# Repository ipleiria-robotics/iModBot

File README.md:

# Apresentação do Projeto 
Este projeto iModBot consiste num robô modular de baixo custo que pode ser programado através de liguagem de programação por blocos e/ou através de linguagem C/C++. Este projeto dispõe de uma biblioteca para facilitar o controlo do robô. 

A programação por blocos divide-se em 4 níveis, para facilitar a aprendizagem do utilizadores. Os níveis são os seguintes:
 - Nível Iniciante -> É possível colocar o robô a efetuar uma terefa com 1 a 2 blocos.
 - Nível Normal -> O utilizador tem mais controlo sob o movimento do robô, dispõe apenas da função loop.
 - Nível Médio -> O utilizador pode agora colocar blocos na função Setup e Loop.
 - Nível Avançado -> O utilizador dispõe de todas as funções da biblioteca e necessita de configurar todos os aspetos do robô.

# Como transferir ficheiros do GitHub
No GitHub não é possível transferir qualquer ficheiro individualmente. É recomendado transferir todas as pastas e ficheiros presentes neste projeto. Para tal siga as instruções abaixo:

Comece por transferir todos os ficheiros no formato .zip

Abra a localização do ficheiro .zip transferido e use um programa para extrair os conteudos

Por fim irá obter um conjunto de pastas e ficheiros organizados da mesma maneira que se encontram neste repositório.

# Elaboração do Projeto
**1º Passo do Projeto**

Para montar o robô basta seguir o documento 4_Guia_de_montagem_offline ([3_Documentacao/3-4_Guia_de_montagem_offline.pdf](https://github.com/ipleiria-robotics/iModBot/blob/master/3_Documentacao/3-4_Guia_de_montagem_offline.pdf)) que mostra como montar ou então assistir o video [iModBot@ipleiria.pt guia de montagem](https://www.youtube.com/watch?v=i4wFh0GqzkM&feature=emb_logo). Este documento também inclui uma listagem de componentes
que serão necessários para a sua montagem. Para perceber melhor o que faz cada componente do robô pode ler o manual técnico ([3_Documentacao/3-5_Manual_Tecnico_iModBot.pdf](https://github.com/ipleiria-robotics/iModBot/blob/master/3_Documentacao/3-5_Manual_Tecnico_iModBot.pdf)) que explica vários aspetos do robô. 

Lista de material:
 * ESP32 wroom32 devkit ; 

 * l293d 4 channel module ;

 * 2x LM393 speed sensor ; 

 * BFD-1000 5CH ;

 * HC-SR04 ;

 * I2C level shifter ; 

 * TP4056 ; 

 * MT3608 ; 

 * li-ion rechargable battery 2500 mAh ; 

 * 2x Breadboard 400 ; 

 * Jumper wire male male, Jumper wire male female ; 

 * 2wd smart robot kit . 

**2º Passo do Projeto** 
 
 Downloads:
 
- Biblioteca iModBot.zip ([4_Biblioteca/iModBot.zip](https://github.com/ipleiria-robotics/iModBot/blob/master/4_Biblioteca/iModBot.zip)) e descompacta o ficheiro. 

- Software Arduino IDE na [pagina do Arduino](https://www.arduino.cc/en/main/software), instale a versão que se adequa ao seu equipamento, para windows recomendamos a opção "Windows installer, for windows 7 and up". 
 -- Tenha em atenção que os conteudos do projeto foram desenvolvidos e testados na versão Arduino IDE 1.8.12, os mesmos deverão continuar ser compatíveis com as versões mais recentes deste software.

- Ficheiro java do ArduBlock ([5_AduBlock/ardublock-beta-20200614.jar](https://github.com/ipleiria-robotics/iModBot/blob/master/5_AduBlock/ardublock-beta-20200614.jar)).

**3º Passo do Projeto**

Ler e seguir os tutoriais para configurar o Arduíno:
 - Configurar Arduíno IDE para o ESP32; ([3_Documentacao/3-1_Como_comunicar_com_o_ESP32.pdf](https://github.com/ipleiria-robotics/iModBot/blob/master/3_Documentacao/3-1_Como_comunicar_com_o_ESP32.pdf))

 - Configurar ArduBlock no Arduíno IDE; ([3_Documentacao/3-2_Como_instalar_ArduBlock_no_Arduino_IDE.pdf](https://github.com/ipleiria-robotics/iModBot/blob/master/3_Documentacao/3-2_Como_instalar_ArduBlock_no_Arduino_IDE.pdf))

 - Como instalar bibliotecas no Arduíno IDE. ([3_Documentacao/3-3_Como_instalar_bibliotecas_no_Arduino_IDE.pdf](https://github.com/ipleiria-robotics/iModBot/blob/master/3_Documentacao/3-3_Como_instalar_bibliotecas_no_Arduino_IDE.pdf))

# Documentação

Após ter o Arduino IDE e o ArduBlock instalados pode usufruir dos tutoriais disponibilizados. Estes tutoriais ensinam a trabalhar com o robô sendo os mesmos divididos em duas categorias: tutoriais para ArduBlock e tutoriais para Arduino IDE.

**Documentação do ArduBlock**

Os [4 níveis](https://github.com/ipleiria-robotics/iModBot/tree/master/1_Tutoriais/1-1_Tuturiais_para_ArduBlock) a baixo irão facilitar e guiar como deve de utilizar cada bloco e como criar um programa.

- [Nivel Iniciante;](https://github.com/ipleiria-robotics/iModBot/blob/master/1_Tutoriais/1-1_Tuturiais_para_ArduBlock/Tutorial_1_-_Nivel%20iniciante/Nivel_iniciante.pdf)

- [Nivel Normal;](https://github.com/ipleiria-robotics/iModBot/blob/master/1_Tutoriais/1-1_Tuturiais_para_ArduBlock/Tutorial_2_-_Nivel_Normal/Nivel_Normal.pdf)

- [Nivel Médio;](https://github.com/ipleiria-robotics/iModBot/blob/master/1_Tutoriais/1-1_Tuturiais_para_ArduBlock/Tutorial_3_-_Nivel_Medio/Nivel_Medio.pdf)

- [Nivel Avançado;](https://github.com/ipleiria-robotics/iModBot/blob/master/1_Tutoriais/1-1_Tuturiais_para_ArduBlock/Tutorial_4_-_Nivel_Avancado/Nivel_Avancado.pdf)

Existe um conjunto de atividades para cada nível. Após ler a documentação de um nível poderá realizar a atividade correspondente  ao mesmo em [2_Atividades/2-1_Atividades_para_ArduBlock/](https://github.com/ipleiria-robotics/iModBot/tree/master/2_Atividades/2-1_Atividades_para_ArduBlock).

**Documentação do Arduino IDE**

Depois de já ter realizado os tutoriais do ArduBock deverá ter uma noção melhor de como programar no Arduino IDE. Também elaboramos alguns tutoriais e atividades para facilitar a aprendizagem,

- [Tutorial 1 - Movimento;](https://github.com/ipleiria-robotics/iModBot/blob/master/1_Tutoriais/1-2_Tutoriais_para_Arduino_IDE/Tutorial_1_-_Movimento/Tutorial_1_iModBot_-_Movimento.pdf)

- [Tutorial 2 - Sensores;](https://github.com/ipleiria-robotics/iModBot/blob/master/1_Tutoriais/1-2_Tutoriais_para_Arduino_IDE/Tutorial_2_-_Sensores/Tutorial_2_iModBot_-_Sensores.pdf)

- [Tutorial 3 - Seguir trajeto.](https://github.com/ipleiria-robotics/iModBot/blob/master/1_Tutoriais/1-2_Tutoriais_para_Arduino_IDE/Tutorial_3_-_Seguir_trajeto/Tutorial_3_iModBot_-_Seguir%20trajeto.pdf)

As atividades para cada tutorial estão disponíveis em [/2_Atividades/2-2_Atividades_para_Arduino_IDE/
](https://github.com/ipleiria-robotics/iModBot/tree/master/2_Atividades/2-2_Atividades_para_Arduino_IDE).

# Editar o ArduBlock

Caso tenha interesse em criar um bloco deve seguir os passos neste pasta [5.Ardublock](https://github.com/ipleiria-robotics/iModBot/blob/master/5_AduBlock/README.md)

# Realidade Aumentada

Utilizando o motor de jogos Unity3d, ROS2 e a nossa biblioteca para o robô, cria o teu mundo virtual, projeta-o no mundo real e vê o robô a interagir com ele.
Esta funcionalidade ainda está em desenvolvimento sendo que por agora ainda é muito limitada. 

# Controladores remotos

Com os controladores das consolas populares PS3 e PS4, consegue controlar o robot à distância via bluetooth. A biblioteca é fácil de instalar e apenas necessita de um programa, o Arduino IDE. Basta colocar valores desejados no código, tanto como sensibilidade de direção, aceleração dos motores, velocidade máxima, e muito mais!

# Autores
 
- Abel Teixeira   - estudante do [Politécnico de Leiria](https://www.ipleiria.pt/cursos/) do curso TeSP em Eletrónica e Redes de Telecomunicações, GitHub: [Ab-Tx](https://github.com/Ab-Tx)
- Samuel Lourenço - estudante do [Politécnico de Leiria](https://www.ipleiria.pt/cursos/) do curso TeSP em Automação, Robótica e manutenção Industrial, GitHub: [SamueLourenc0](https://github.com/SamueLourenc0)
- Nelson Henriques - estudante do [Politécnico de Leiria](https://www.ipleiria.pt/cursos/) do curso TeSP em Automação, Robótica e manutenção Industrial, GitHub: [NetchoExtreme](https://github.com/NetchoExtreme)
- Paulo Sousa - estudante do [Politécnico de Leiria](https://www.ipleiria.pt/cursos/) do curso TeSP em Eletrónica e Redes de Telecomunicações, GitHub [DimitriOnLSD](https://github.com/DimitriOnLSD)

## Orientado por:
- Luís Conde - [Politécnico de Leiria](https://www.ipleiria.pt), GitHub: [Luís Conde](https://github.com/conde-ISR-UC-PT)
- Carlos Neves - [Politécnico de Leiria](https://www.ipleiria.pt), [INESC-Coimbra](http://inescc.estg.ipleiria.pt/), GitHub: [Carlos Neves](https://github.com/carlos-neves)

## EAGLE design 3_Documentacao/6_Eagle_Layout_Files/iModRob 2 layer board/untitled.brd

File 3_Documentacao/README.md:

# Documentação

Nesta pasta pode encontrar documentação para varios aspetos do projeto.

- **3.1_Como_comunicar_com_o_ESP32.pdf**
  - Explica como conectar a placa de desenvolvimento ESP32 ao software Arduino IDE.
  
- **3.2_Como_instalar_ArduBlock_no_Arduino_IDE.pdf**
  - Explica como instalar o ArduBlock no software Arduino IDE.
  
- **3.3_Como_instalar_bibliotecas_no_Arduino_IDE.pdf**
  - Explica como instalar biblioteacas no software Arduino IDE.
  
- **3.4_Guia_de_montagem_offline.pdf**
  - Fornece uma lista de componentes e apresenta as ligações que devem ser efetuadas entre os componentes.
  
- **3.5_Manual_Tecnico_iModBot.pdf**
  - Descreve os componentes utilizados no projeto, as funções proporcionadas pela biblioteca entre outros aspetos.
  
- **3.6_iModRob_Eagle_2_layer_board.zip**
  - Também é disponibilizado o projeto para a aplicação Autodesk Eagle que contém uma placa de circuito impresso (PCB) que facilitará a montagem dos componentes no robô.

- **3.7_Listagem_de_componentes_mais_links_de_compra_auxiliares**
  - Também é disponibilizado uma lista de componentes completa a incluir links de lojas online onde poderas encontrar os componentes em custos mais baratos.

- **3.8_ArduBlock2020**
  - Para começar a programar o robô por blocos, basta seguir o tutorial 3.3_Como_instalar_ArduBlock_no_Arduino_IDE.pdf e deve ser usado este ficheiro para ter os blocos prontos para programar o robô.

- **3.8_Guia_basica_de_montagem_de_circuitos_eletricos**
  - É fornecida uma guia basica de montagem para conhecer a Breadboard e o seu funcionamento de face à montagem de placas eletrónicas nesta ferramenta.
  
# Esquema eletrónico e PCB

  - Foram inseridos vários pontos de teste na placa de circuito impresso. 
  - Foram adicionados jumpers para poder desconectar a alimentação geral do circuito e/ou a alimentação da placa de desenvolvimento DOIT ESP32 Devkit V1 e/ou a alimentação do módulo baseado no integrado L293D.

**Esquema eletrónico**:

**Placa de circuito impresso** (sem o plano de massa visível):

    Uma boa opção para conectar/desconectar a alimentação seria o uso de conectores "jumper two pins".

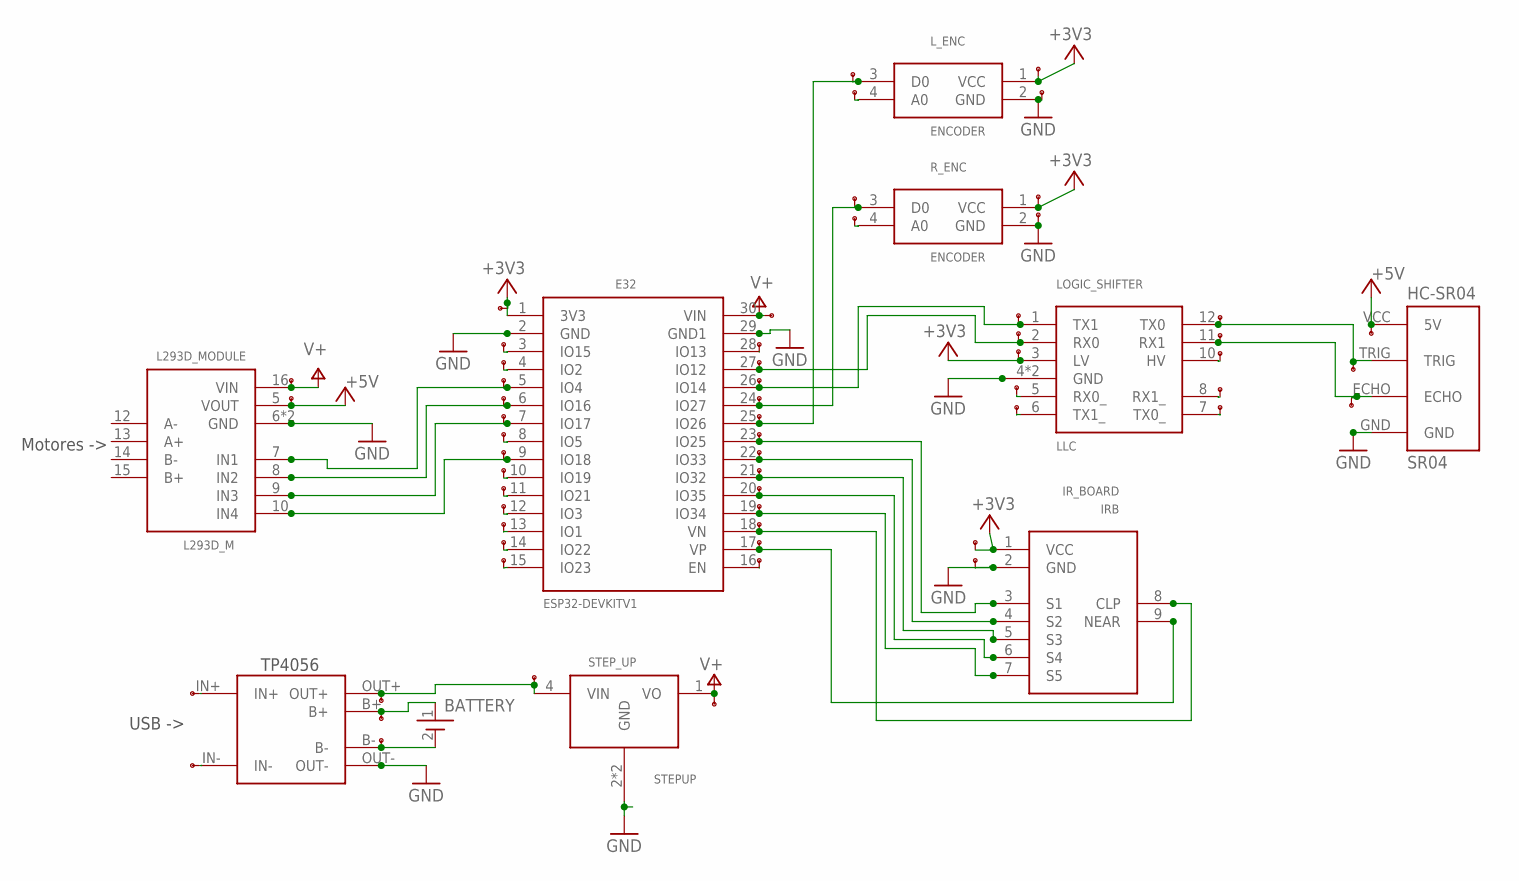
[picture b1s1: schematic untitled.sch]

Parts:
BATTERY: BAT_PAD
BAT_CHARGER: TP4056-MODULE; TP4056-LITHIUM-PROTECTED-MODULE
E32: ESP32DEVKITV1; ESP32-DEVKITV1
IR_BOARD: IRB
L293D_MODULE: L293D_M
LOGIC_SHIFTER: LLC
L_ENC: ENCODER
R_ENC: ENCODER
SR04: HC-SR04; HC-SR04_FOOTPRINT
STEP_UP: STEPUP
U$1, U$2, U$3, U$4, U$8, U$10, U$11, U$12, U$13, U$14, U$15, U$16, U$17, U$18, U$19, U$20, U$21, U$22, U$23, U$24, U$25, U$26, U$27, U$28, U$29, U$30, U$31, U$32, U$33, U$34, U$36, U$37, U$38, U$40, U$41, U$42, U$43, U$44, U$46, U$47, U$48, U$49, U$50, U$51, U$52, U$53, U$54, U$55, U$56, U$57, U$59, U$60, U$61, U$62, U$63, U$64, U$65, U$67, U$68, U$69: TP

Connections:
+3V3: E32.1 (3V3), IR_BOARD.1 (VCC), LOGIC_SHIFTER.3 (LV), L_ENC.1 (VCC), R_ENC.1 (VCC), U$3.P$1, U$8.P$1, U$49.P$1, U$51.P$1, U$57.P$1
+5V: L293D_MODULE.5 (VOUT), SR04.VCC (5V), U$2.P$1, U$69.P$1
GND: BAT_CHARGER.OUT-, E32.2 (GND), E32.29 (GND1), IR_BOARD.2 (GND), L293D_MODULE.6 (GND), L293D_MODULE.11 (GND), LOGIC_SHIFTER.4 (GND), LOGIC_SHIFTER.9 (GND), L_ENC.2 (GND), R_ENC.2 (GND), SR04.GND, STEP_UP.2 (GND), STEP_UP.3 (GND), U$4.P$1, U$50.P$1, U$52.P$1
unnamed: E32.5 (IO4), L293D_MODULE.7 (IN1), U$46.P$1
unnamed: E32.6 (IO16), L293D_MODULE.8 (IN2), U$12.P$1
unnamed: E32.7 (IO17), L293D_MODULE.9 (IN3), U$13.P$1
unnamed: E32.9 (IO18), L293D_MODULE.10 (IN4), U$15.P$1
unnamed: BATTERY.1 (+), BAT_CHARGER.B+, U$41.P$1
unnamed: BATTERY.2 (-), BAT_CHARGER.B-, U$40.P$1
unnamed: BAT_CHARGER.OUT+, STEP_UP.4 (VIN), U$42.P$1, U$43.P$1
unnamed: E32.23 (IO25), IR_BOARD.3 (S1), U$29.P$1
unnamed: E32.22 (IO33), IR_BOARD.4 (S2), U$28.P$1
unnamed: E32.21 (IO32), IR_BOARD.5 (S3), U$27.P$1
unnamed: E32.20 (IO35), IR_BOARD.6 (S4), U$26.P$1
unnamed: E32.19 (IO34), IR_BOARD.7 (S5), U$25.P$1
unnamed: E32.17 (VP), IR_BOARD.9 (NEAR), U$23.P$1
unnamed: E32.18 (VN), IR_BOARD.8 (CLP), U$24.P$1
unnamed: E32.27 (IO12), LOGIC_SHIFTER.2 (RX0), U$33.P$1, U$56.P$1
unnamed: E32.26 (IO14), LOGIC_SHIFTER.1 (TX1), U$32.P$1, U$55.P$1
unnamed: LOGIC_SHIFTER.12 (TX0), SR04.TRIG, U$65.P$1, U$68.P$1
unnamed: LOGIC_SHIFTER.11 (RX1), SR04.ECHO, U$64.P$1, U$67.P$1
unnamed: E32.24 (IO27), R_ENC.3 (D0), U$31.P$1, U$54.P$1
unnamed: E32.25 (IO26), L_ENC.3 (D0), U$30.P$1, U$47.P$1
unnamed: E32.15 (IO23), U$21.P$1
unnamed: E32.3 (IO15), U$10.P$1
unnamed: E32.4 (IO2), U$11.P$1
unnamed: E32.8 (IO5), U$14.P$1
unnamed: E32.10 (IO19), U$16.P$1
unnamed: E32.11 (IO21), U$17.P$1
unnamed: E32.12 (IO3), U$18.P$1
unnamed: E32.13 (IO1), U$19.P$1
unnamed: E32.14 (IO22), U$20.P$1
unnamed: E32.16 (EN), U$22.P$1
unnamed: E32.28 (IO13), U$34.P$1
unnamed: BAT_CHARGER.IN-, U$38.P$1
unnamed: BAT_CHARGER.IN+, U$37.P$1
unnamed: LOGIC_SHIFTER.5 (RX0_), U$59.P$1
unnamed: LOGIC_SHIFTER.6 (TX1_), U$60.P$1
unnamed: LOGIC_SHIFTER.7 (TX0_), U$61.P$1
unnamed: LOGIC_SHIFTER.8 (RX1_), U$62.P$1
unnamed: LOGIC_SHIFTER.10 (HV), U$63.P$1
unnamed: R_ENC.4 (A0), U$53.P$1
unnamed: L_ENC.4 (A0), U$48.P$1
V+: E32.30 (VIN), L293D_MODULE.16 (VIN), STEP_UP.1 (VO), U$1.P$1, U$36.P$1, U$44.P$1

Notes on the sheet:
USB ->
Motores ->
TP4056

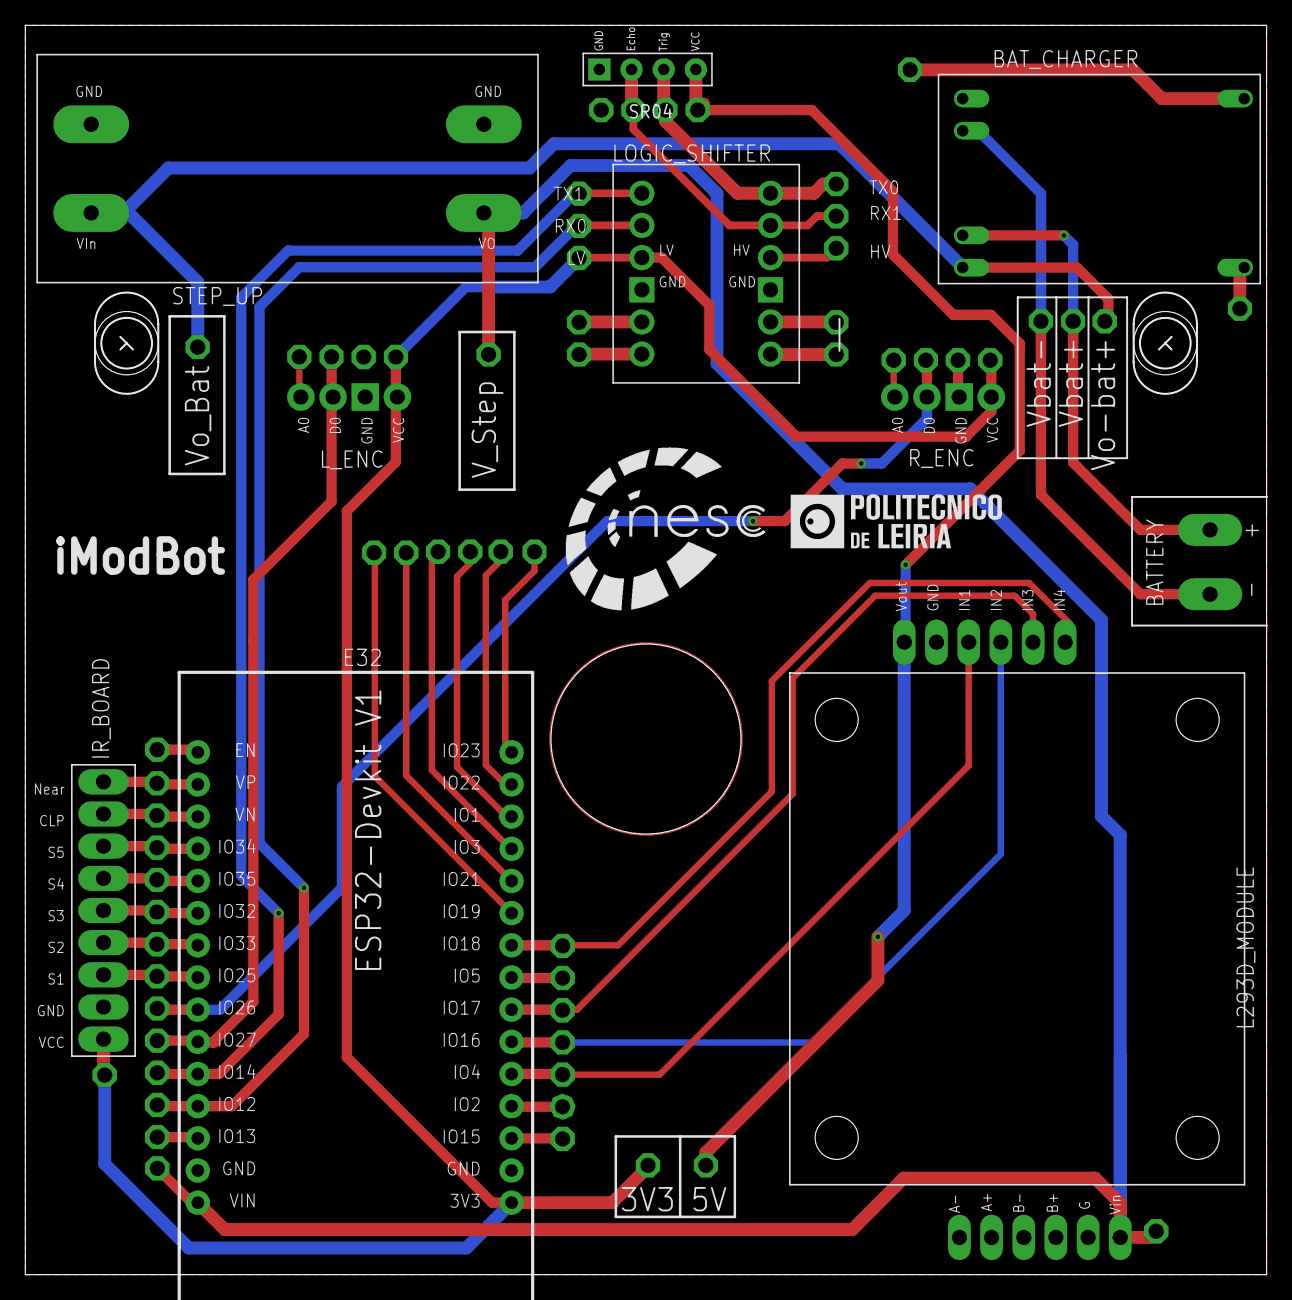
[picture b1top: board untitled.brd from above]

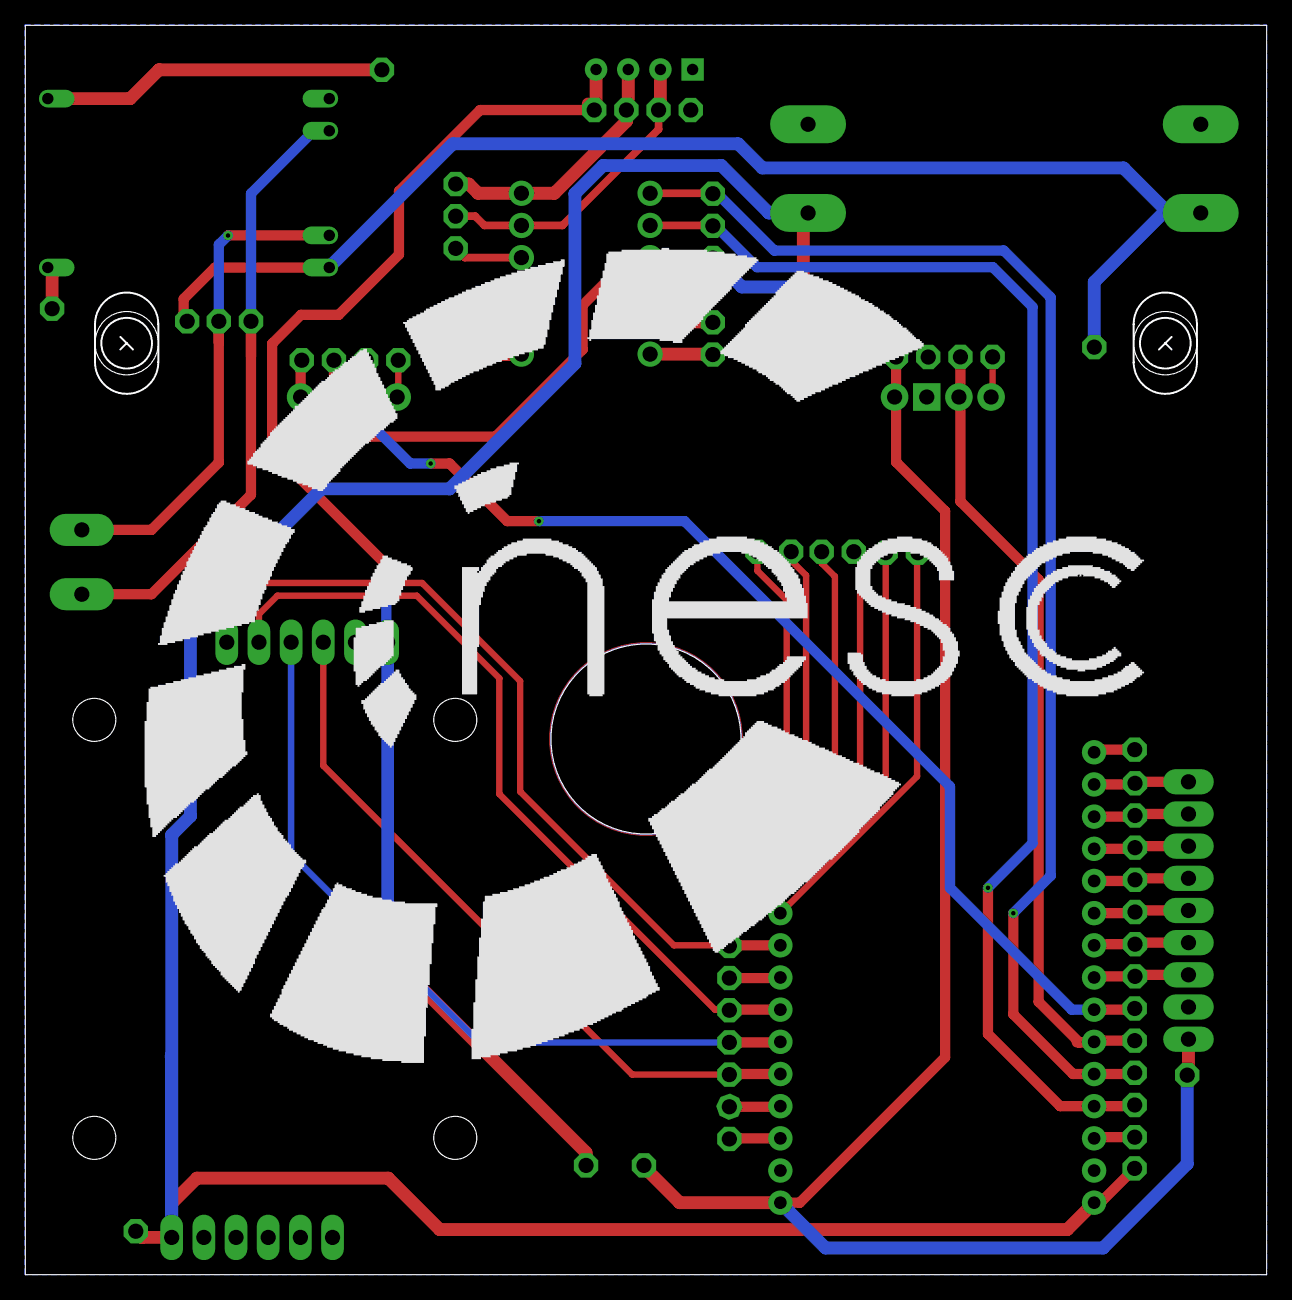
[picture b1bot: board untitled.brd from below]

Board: 2 copper layers, 97.8 x 98.5 mm, 70 parts (2 on the bottom side), 44 nets.

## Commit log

2020-06-08 structure upload
2020-06-08 Docs update
2020-06-08 new files upload
2020-06-09 Multiple files upload
2020-06-12 content match
2020-06-12 lib update
2020-06-12 mensagem
2020-06-25 Eagle project update
2020-06-25 Tutorial 1 update
2020-06-25 Names of tutorial files changed
2020-06-25 Tutorial 2 update
2020-06-25 Tutorial 3 update
2020-06-25 ArduBlock Tutorial name changes
2020-06-25 ArduBlock Activities name changes
2020-06-25 Tut 1 files update
2020-06-25 Activity 2 update
2020-06-25 Activities update
2020-06-26 file updated
2020-06-26 decription files added
2020-06-26 name changes
2020-06-26 description added
2020-06-29 library examples update
2020-06-29 examples updated
2020-07-02 Tutorials update
2020-07-09 Eagle Files updated
2020-12-09 Create Robo
2020-12-19 Bugfix
2021-03-12 Add files
2021-03-12 Upload tutorials
2021-07-15 reverse bugfix
2021-07-15 Update Tuturiais
2021-07-15 Update atividades
2021-07-15 Update documentacao
2021-07-15 update ardublock
2021-07-15 add realidade aumentada
2021-07-15 Tutorial update
2021-07-25 Add Links
2021-08-02 missing lib and fmod fix
2022-06-21 spelling
    spelling correction
2022-06-21 Updated tutorials
    Switched original language to English
2022-06-21 Updated activities
    Switched original language to English
2022-06-21 Updated documents
    Documents folder now contains all pdf's necessary to implement a functional iModBot or help the user in troubleshooting
2022-06-21 Added files
    Added folder files to easier use
    PCB files
    Battery Case 3D files
    Libraries
    Ardublock files
2022-06-21 Updated AR folder
    AR folder only
2022-06-21 Updated documents
    spelling error
2022-06-23 bug fix ramp generator
    Fixed a bug with ramp generator not accepting values
    Added non .rar files
2022-06-23 double battery case v2
    Improved version for Double battery case
2022-06-24 removed old versions
2022-06-24 update bc
2022-06-24 update battery case
2022-06-24 dualshock guide
2022-06-24 version 2 EAGLE sch
2022-06-24 update readme
    Updated PCB Files readme.md
    Updated Libraries readme.md
    Updated ArduBlock readme.md
2022-06-24 update readme
    Added new author
    Added new title for the controllers and some information
2022-06-24 update docs
    Better organization inside Documents folder
2022-06-28 update tutorials
    Added source docx files
2022-06-28 update activities
    Added source docx files
2022-06-28 update documents
    Added various documents
    Added source docx files
2022-06-28 update files
    Added PCB Files
    Added battery case files
    Added ArduBlock files
    Added libraries
    Update readme file
2022-06-28 update AR
    Update folder
2022-06-28 update readme.md
    docs link bug
2022-06-28 update readme.md
    Added src folder info
2022-06-28 update readme.md
    Bug fix
2022-07-02 update files
2022-07-02 side support motor
2022-07-04 pcb v1.2
2022-07-07 pcb v1.3
    Adjusted 3PDT Switch
    Top Silk holes
    Testpoint features charge voltage
    Text size increased
    Battery text moved
    Added text logic shifter
2022-07-07 pcb v1.31
2022-07-10 PCB v1.03.4
2022-07-13 UWB ILS
    Ultra-Wideband Indoor Location System
2022-07-13 esp32-mdek workspace
2022-07-13 esp32-mdek UART
2022-07-14 Android APK
2022-07-14 Original Firmware
2022-07-14 missing files
2022-07-14 missing apk and hex files
2022-07-14 bug fix putchar
2022-07-14 bug fix emSession
